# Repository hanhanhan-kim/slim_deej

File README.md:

# Slim Deej

*A small form factor Deej that frees up desk space.*

This project provides hardware for the awesome [Deej](https://github.com/omriharel/deej) volume mixer (Windows and Linux only). The Deej community has come up with many myriad designs, but I didn't find one that suited my needs. So I made one! This Deej design is fairly low profile, and can be mounted under one's desk or monitor, so it doesn't take up any valuable desk space. For this reason, I'm using rotary potentiometers, because sliding potentiometers take up a lot of real estate. I also designed a PCB, to ease the assembly process, and slim down the form factor. A slight upward angle on the front panel adds to the aesthetic. The original [`.f3d` ](./3d_files/case_front.f3d) file is parameterized, however, and so the angle can be easily adjusted. For example, a 90 degree version is available [here](). 

## BOM

In addition to standard electronics equipment and access to a 3D-printer:

| Item                          | Price (USD) | Quantity | Source                                                       |
| ----------------------------- | ----------- | -------- | ------------------------------------------------------------ |
| Arduino Pro Micro*            | 27.99 / 3   | 1        | Amazon<br />[ASIN B01MTU9GOB](https://www.amazon.com/HiLetgo-Atmega32U4-Bootloadered-Development-Microcontroller/dp/B01MTU9GOB/ref=sr_1_1_sspa?dchild=1&keywords=arduino+pro+micro&qid=1614562625&sr=8-1-spons&psc=1&spLa=ZW5jcnlwdGVkUXVhbGlmaWVyPUEyV1BVTFBUNEY2NjhHJmVuY3J5cHRlZElkPUEwMTk3NDQwM1RON1BNTkJSNjBGSyZlbmNyeXB0ZWRBZElkPUEwMzI5Nzg0MlpFV1c0TUtIVElGWSZ3aWRnZXROYW1lPXNwX2F0ZiZhY3Rpb249Y2xpY2tSZWRpcmVjdCZkb05vdExvZ0NsaWNrPXRydWU=) |
| PCB                           | 5.40 / 5    | 1        | [JLCPCB](https://jlcpcb.com/)                                |
| Rotary potentiometer (10 kΩ ) | 2.23        | 5        | [Digikey 987-1666-ND](https://www.digikey.com/en/products/detail/tt-electronics-bi/P0915N-EC15BR10K/4780755?s=N4IgTCBcDaIJwA4DsBaAjANiygdgExAF0BfIA) |
| *Optional*: Knobs             | 0 - lots    | 5        | Can be printed (e.g. [here](https://www.thingiverse.com/thing:54024) or [here](https://www.thingiverse.com/thing:1072393)), or bought. Just make sure it's for 6 mm diameter shafts. Guitar knobs are often of the correct size. |

**Note*: I used an Arduino Pro Micro clone, to cut down on price. Any microcontroller with the ATmega 32U4 processor and a Pro Micro footprint and pinout should be fine, e.g. the [Sparkfun Pro Micro](https://www.sparkfun.com/products/12640). Unfortunately, the supply chain shortage has affected things, and microcontrollers are more expensive than they used to be.

## Circuit

Here's a schematic of the circuit. It's very simple, just a GND rail and a VCC rail, and each potentiometer gets its own analog pin:

Here's the circuit PCB, with a view from the back side: 

The KiCad source files are available [here](./kicad_slim_deej/). 

## Installation

Installation is fairly straightforward. Print the [panel case](./3d_files/case_front.3mf), a render of which is shown: 

Solder the rotary potentiometers *first*. Then solder the microcontroller onto the other side of the PCB (only one side of the microcontroller pins will be soldered onto the PCB). Make sure the USB port is facing the text, like so:

Then, using the washers and nuts that come with the potentiometers to affix the PCB to the case:

Then, upload the [firmware provided](./arduino_deej_5_knobs/arduino_deej_5_knobs.ino), using the Arduino IDE. This firmware differs from the [one in the official Deej Github repo](https://github.com/omriharel/deej/tree/master/arduino/deej-5-sliders-vanilla), only in that the specified pins correspond to the potentiometers, from left to right on the panel. Finally, download the [Deej software and configuration file](https://github.com/omriharel/deej/releases/tag/v0.9.10) from the official Deej repo, and make sure the Deej configuration file specifies the correct port. Then, edit the configuration file to your heart's desire, and enjoy your Deej! Read the [official Deej docs](https://github.com/omriharel/deej#software) for more details! The Slim Deej can be mounted with a command strip (my preferred method), or hot glue, or whatever tickles your fancy.

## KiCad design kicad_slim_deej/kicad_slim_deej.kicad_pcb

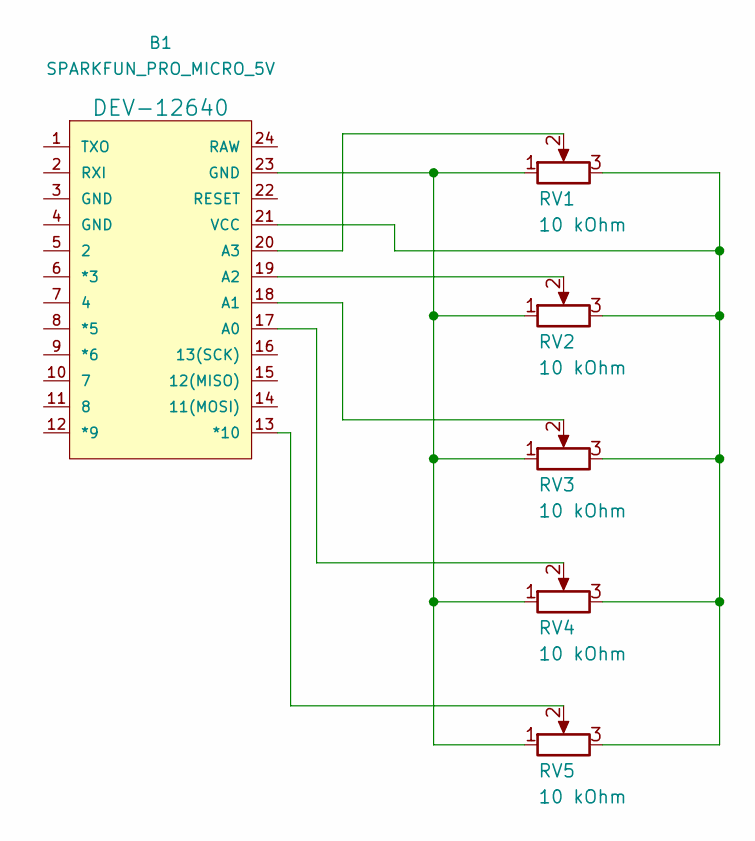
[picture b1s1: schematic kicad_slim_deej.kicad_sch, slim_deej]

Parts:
B1: SPARKFUN_PRO_MICRO_5V; SPARKFUN_PRO_MICRO_ANALOG_HALF
RV1, RV2, RV3, RV4, RV5: 10 kOhm; R0904N

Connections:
unnamed: B1.13 (*10), RV5.2
unnamed: B1.17 (A0), RV4.2
unnamed: B1.18 (A1), RV3.2
unnamed: B1.19 (A2), RV2.2
unnamed: B1.20 (A3), RV1.2
unnamed: B1.21 (VCC), RV1.3, RV2.3, RV3.3, RV4.3, RV5.3
unnamed: B1.23 (GND), RV1.1, RV2.1, RV3.1, RV4.1, RV5.1

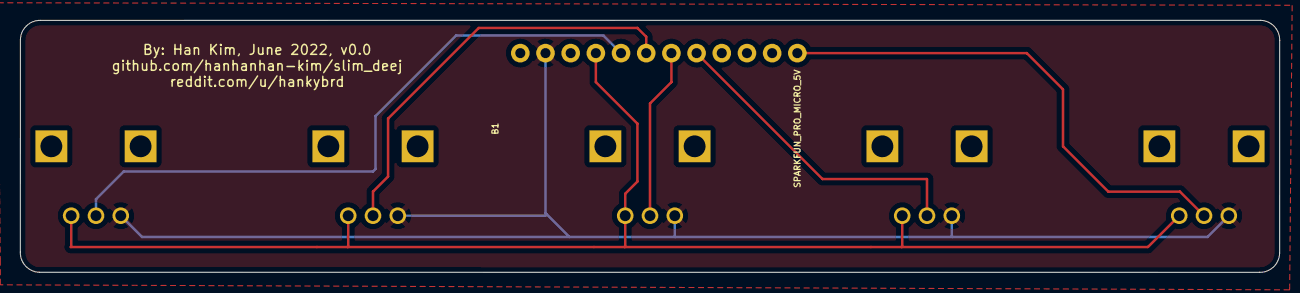
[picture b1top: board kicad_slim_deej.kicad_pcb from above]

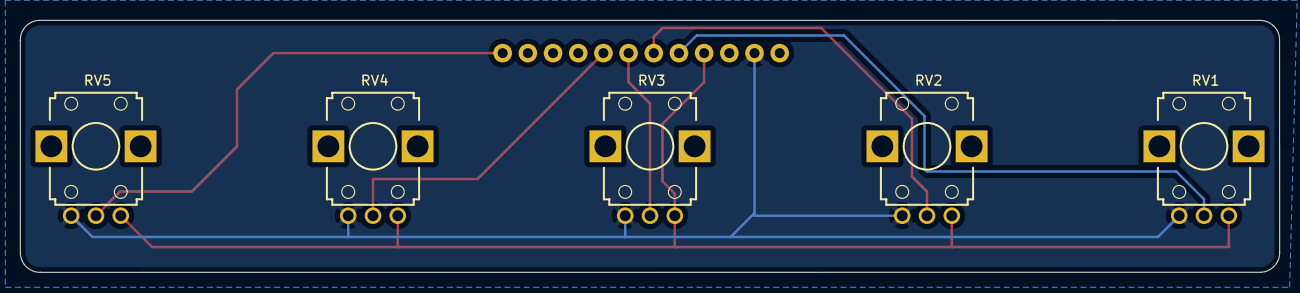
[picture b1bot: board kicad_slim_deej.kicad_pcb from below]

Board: 2 copper layers, 127.0 x 25.4 mm, 6 parts (5 on the bottom side), 7 nets.

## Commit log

2022-06-29 init
    - add PCB design
    - add case design
    - first time doing multiline commits! hehe
2022-07-03 recentre hole positions
2022-07-15 adjust case and add firmware: - make case panel front thinner, so that the threads of the pots can extend past the case - add firmware with correct knob order from left to right
2022-07-15 rename some files and add docs
2022-07-15 add license
2022-07-15 add gitignore
2022-07-15 fix link to .ino
2022-07-15 add mounted img
2022-07-17 add more 3dp files and change license: - change license on kicad schematic to CC (NC-SA) - add .f3z and .step files of case front panel - update readme to reflect these changes
2022-07-21 add 90 deg alt
2023-11-12 add mounting holes + file for sheet metal

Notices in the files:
kicad_slim_deej/kicad_slim_deej.kicad_pcb:
gnu.org/licenses/gpl-3.0.html
License GPL by 3.0
